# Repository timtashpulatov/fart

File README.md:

# fart
Flash Cartridge for Fairchild Channel F

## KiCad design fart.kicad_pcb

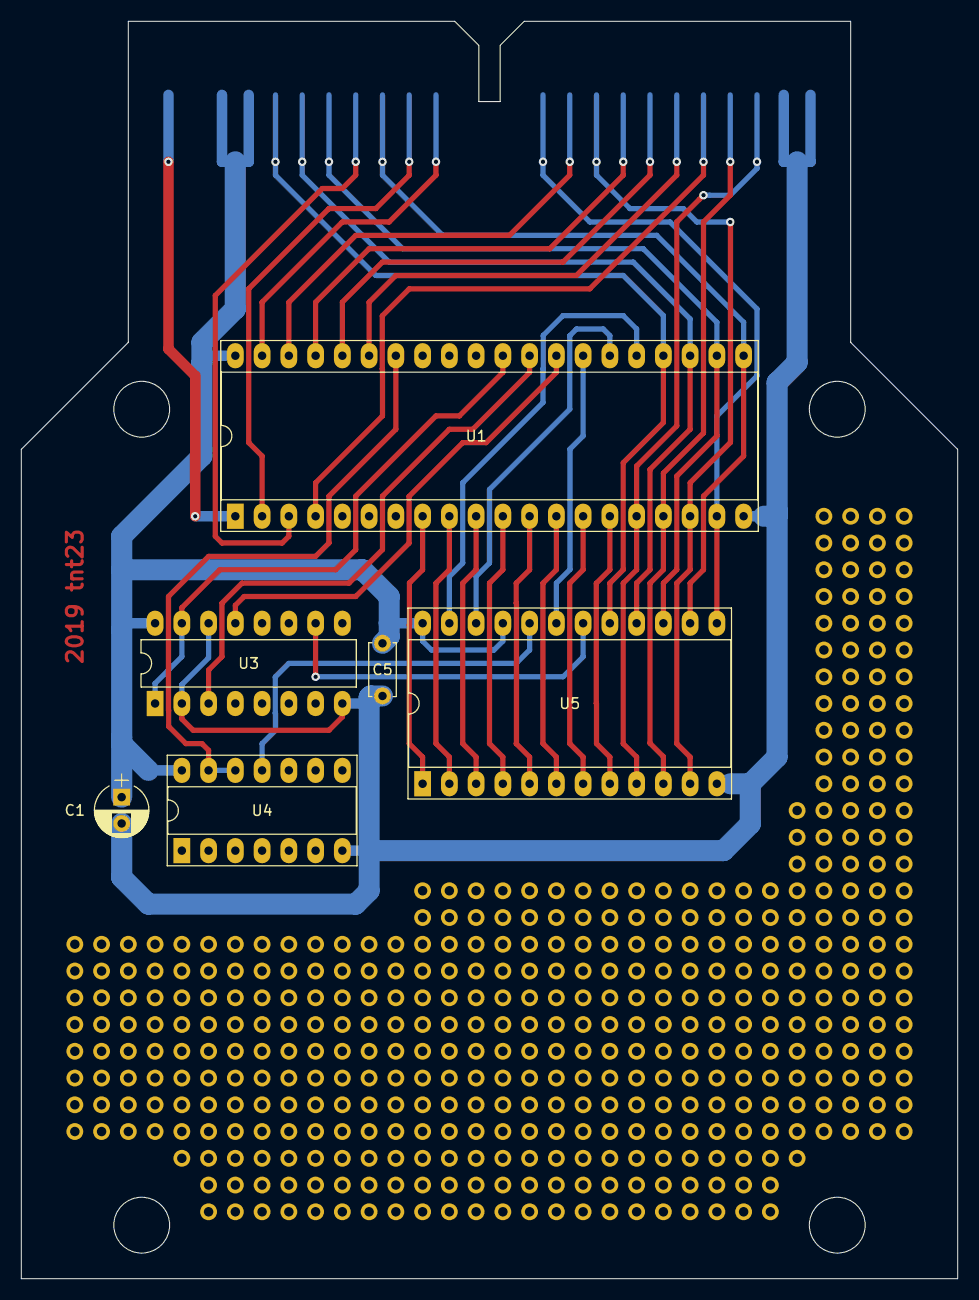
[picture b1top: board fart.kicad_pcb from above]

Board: 2 copper layers, 88.9 x 119.4 mm, 7 parts (1 on the bottom side), 36 nets.

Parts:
C1: 47uF 16V; CP_Radial_D5.0mm_P2.50mm
C5: 100nF; C_Disc_D5.0mm_W2.5mm_P5.00mm
U1: F3853; DIP-40_W15.24mm_Socket_LongPads
U3: 74156; DIP-16_W7.62mm_LongPads
U4: 74LS00; DIP-14_W7.62mm_Socket_LongPads
U5: AT28C16; DIP-24_W15.24mm_Socket_LongPads
X1: CartConn; Cart_Conn

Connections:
+5V: C1.1, C5.1, U1.40, U3.16, U5.21, U5.24, X1.19, X1.20
+12V: U1.1, X1.22
/08xx: U3.10, U5.18
/A0: U1.15, U5.8
/A1: U1.14, U5.7
/A2: U1.13, U5.6
/A3: U1.12, U5.5
/A4: U1.11, U5.4
/A5: U1.10, U5.3
/A6: U1.9, U5.2
/A7: U1.8, U5.1
/A8: U1.25, U5.23
/A9: U1.26, U5.22
/A10: U1.27, U5.19
/A11: U1.28, U3.13
/A12: U1.29, U3.3
/A13: U1.30, U3.1, U3.15
/CPU_READ: U1.34, U4.12, U4.13
/D0: U1.16, U5.9, X1.3
/D1: U1.17, U5.10, X1.4
/D2: U1.18, U5.11, X1.9
/D3: U1.19, U5.13, X1.11
/D4: U1.21, U5.14, X1.14
/D5: U1.22, U5.15, X1.16
/D6: U1.23, U5.16, X1.17
/D7: U1.24, U5.17, X1.18
/PHI: U1.2, X1.13
/ROMC0: U1.35, X1.6
/ROMC1: U1.36, X1.7
/ROMC2: U1.37, X1.8
/ROMC3: U1.38, X1.10
/ROMC4: U1.39, X1.12
/WRITE: U1.3, X1.15
/~CPU_READ: U4.11, U5.20
/~INTREQ: U1.4, X1.5
GND: C1.2, C5.2, U1.20, U3.2, U3.8, U3.14, U5.12, X1.1, X1.2

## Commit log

2019-07-04 Kicad project
2019-07-04 Create test
2019-07-04 PCB update
2019-07-05 Update PCB and socket 3d model
2019-07-05 Add EEPROM and address decoder
2019-07-05 Minor update
2019-07-07 Massive update
2019-07-07 Rough routing done
2019-07-07 Add credentials
2019-07-07 Gerbers!
2019-07-07 Create pops
2019-07-07 Silk update
2019-07-13 Fixed wrong chip select (was on 2800h instead of 0800h)
